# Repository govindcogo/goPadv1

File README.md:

# The 4-Key GoPad
Hello! This is my submission for hackpad! This was made for Hack Club's highway to undercity.
## Features

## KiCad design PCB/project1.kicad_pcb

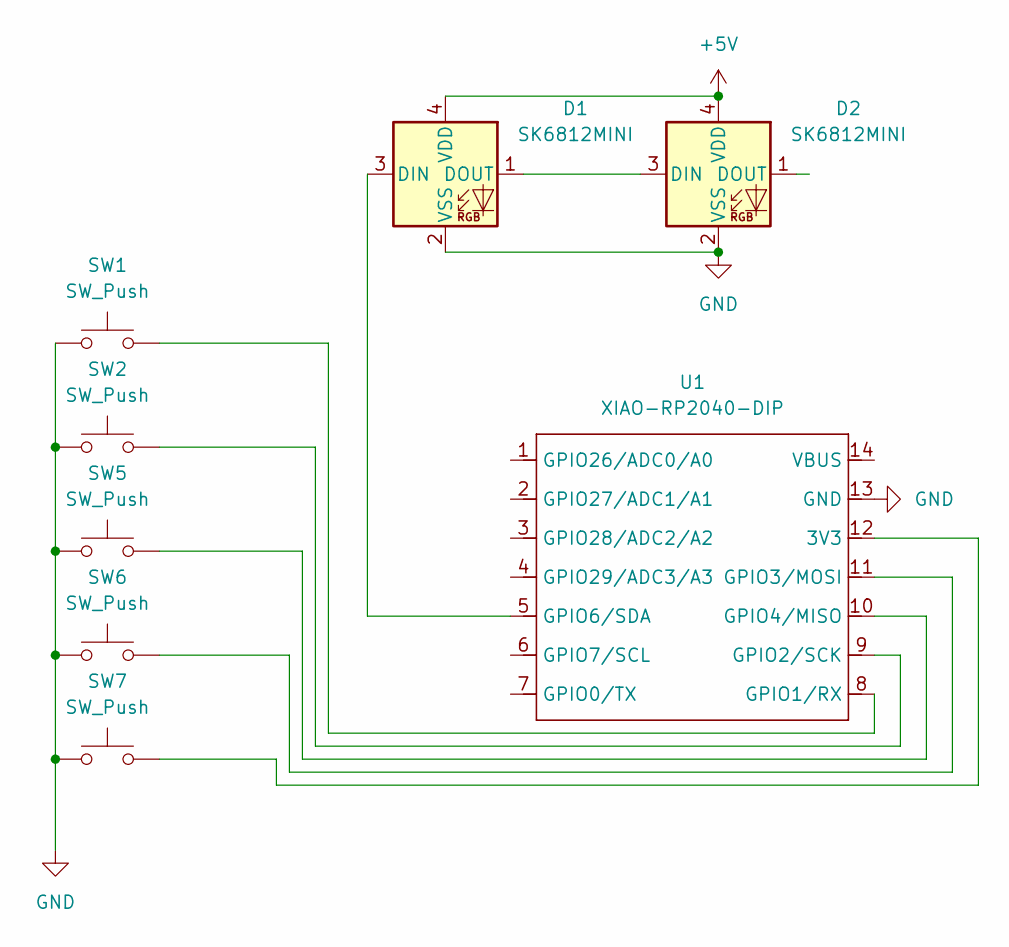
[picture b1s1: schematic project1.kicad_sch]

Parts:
D1, D2: SK6812MINI; LED_SK6812MINI_PLCC4_3.5x3.5mm_P1.75mm
SW1, SW2, SW5, SW6, SW7: SW_Push; SW_Cherry_MX_1.00u_PCB
U1: XIAO-RP2040-DIP

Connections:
+5V: D1.4 (VDD), D2.4 (VDD)
GND: D1.2 (VSS), D2.2 (VSS), SW1.2, SW2.1, SW5.1, SW6.1, SW7.1, U1.13 (GND)
unnamed: D1.3 (DIN), U1.5 (GPIO6/SDA)
unnamed: D1.1 (DOUT), D2.3 (DIN)
unnamed: SW7.2, U1.12 (3V3)
unnamed: SW1.1, U1.8 (GPIO1/RX)
unnamed: SW2.2, U1.9 (GPIO2/SCK)
unnamed: SW6.2, U1.11 (GPIO3/MOSI)
unnamed: SW5.2, U1.10 (GPIO4/MISO)

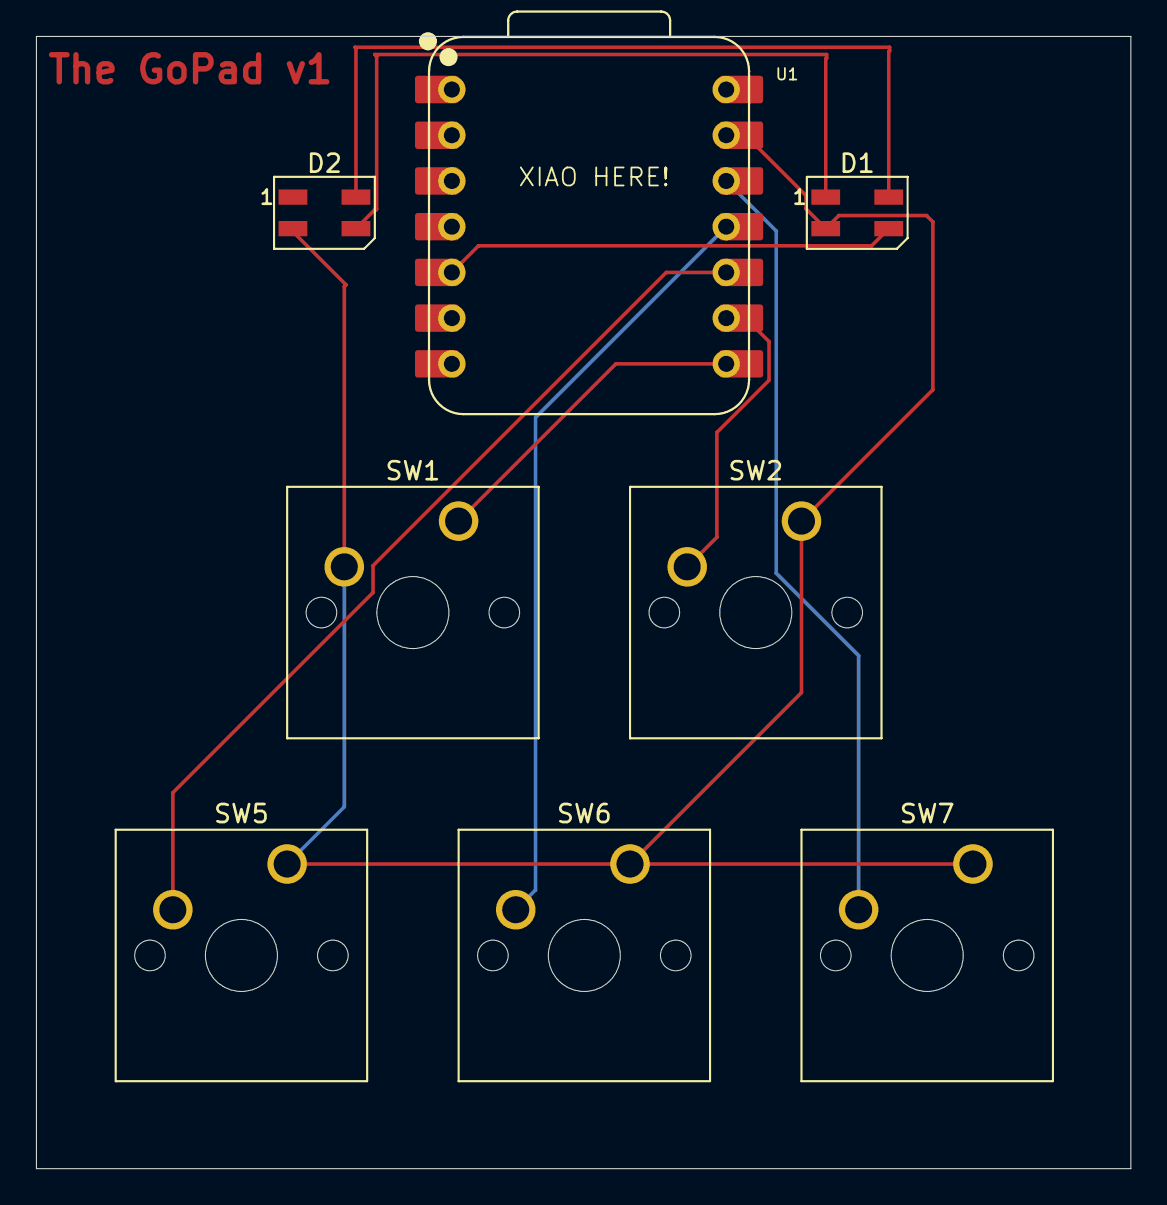
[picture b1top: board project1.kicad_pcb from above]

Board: 2 copper layers, 60.8 x 62.9 mm, 8 parts (0 on the bottom side), 9 nets.

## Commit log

2025-06-07 Create CAD
2025-06-07 Create PCB
2025-06-07 Create Firmware
2025-06-07 Create temp
